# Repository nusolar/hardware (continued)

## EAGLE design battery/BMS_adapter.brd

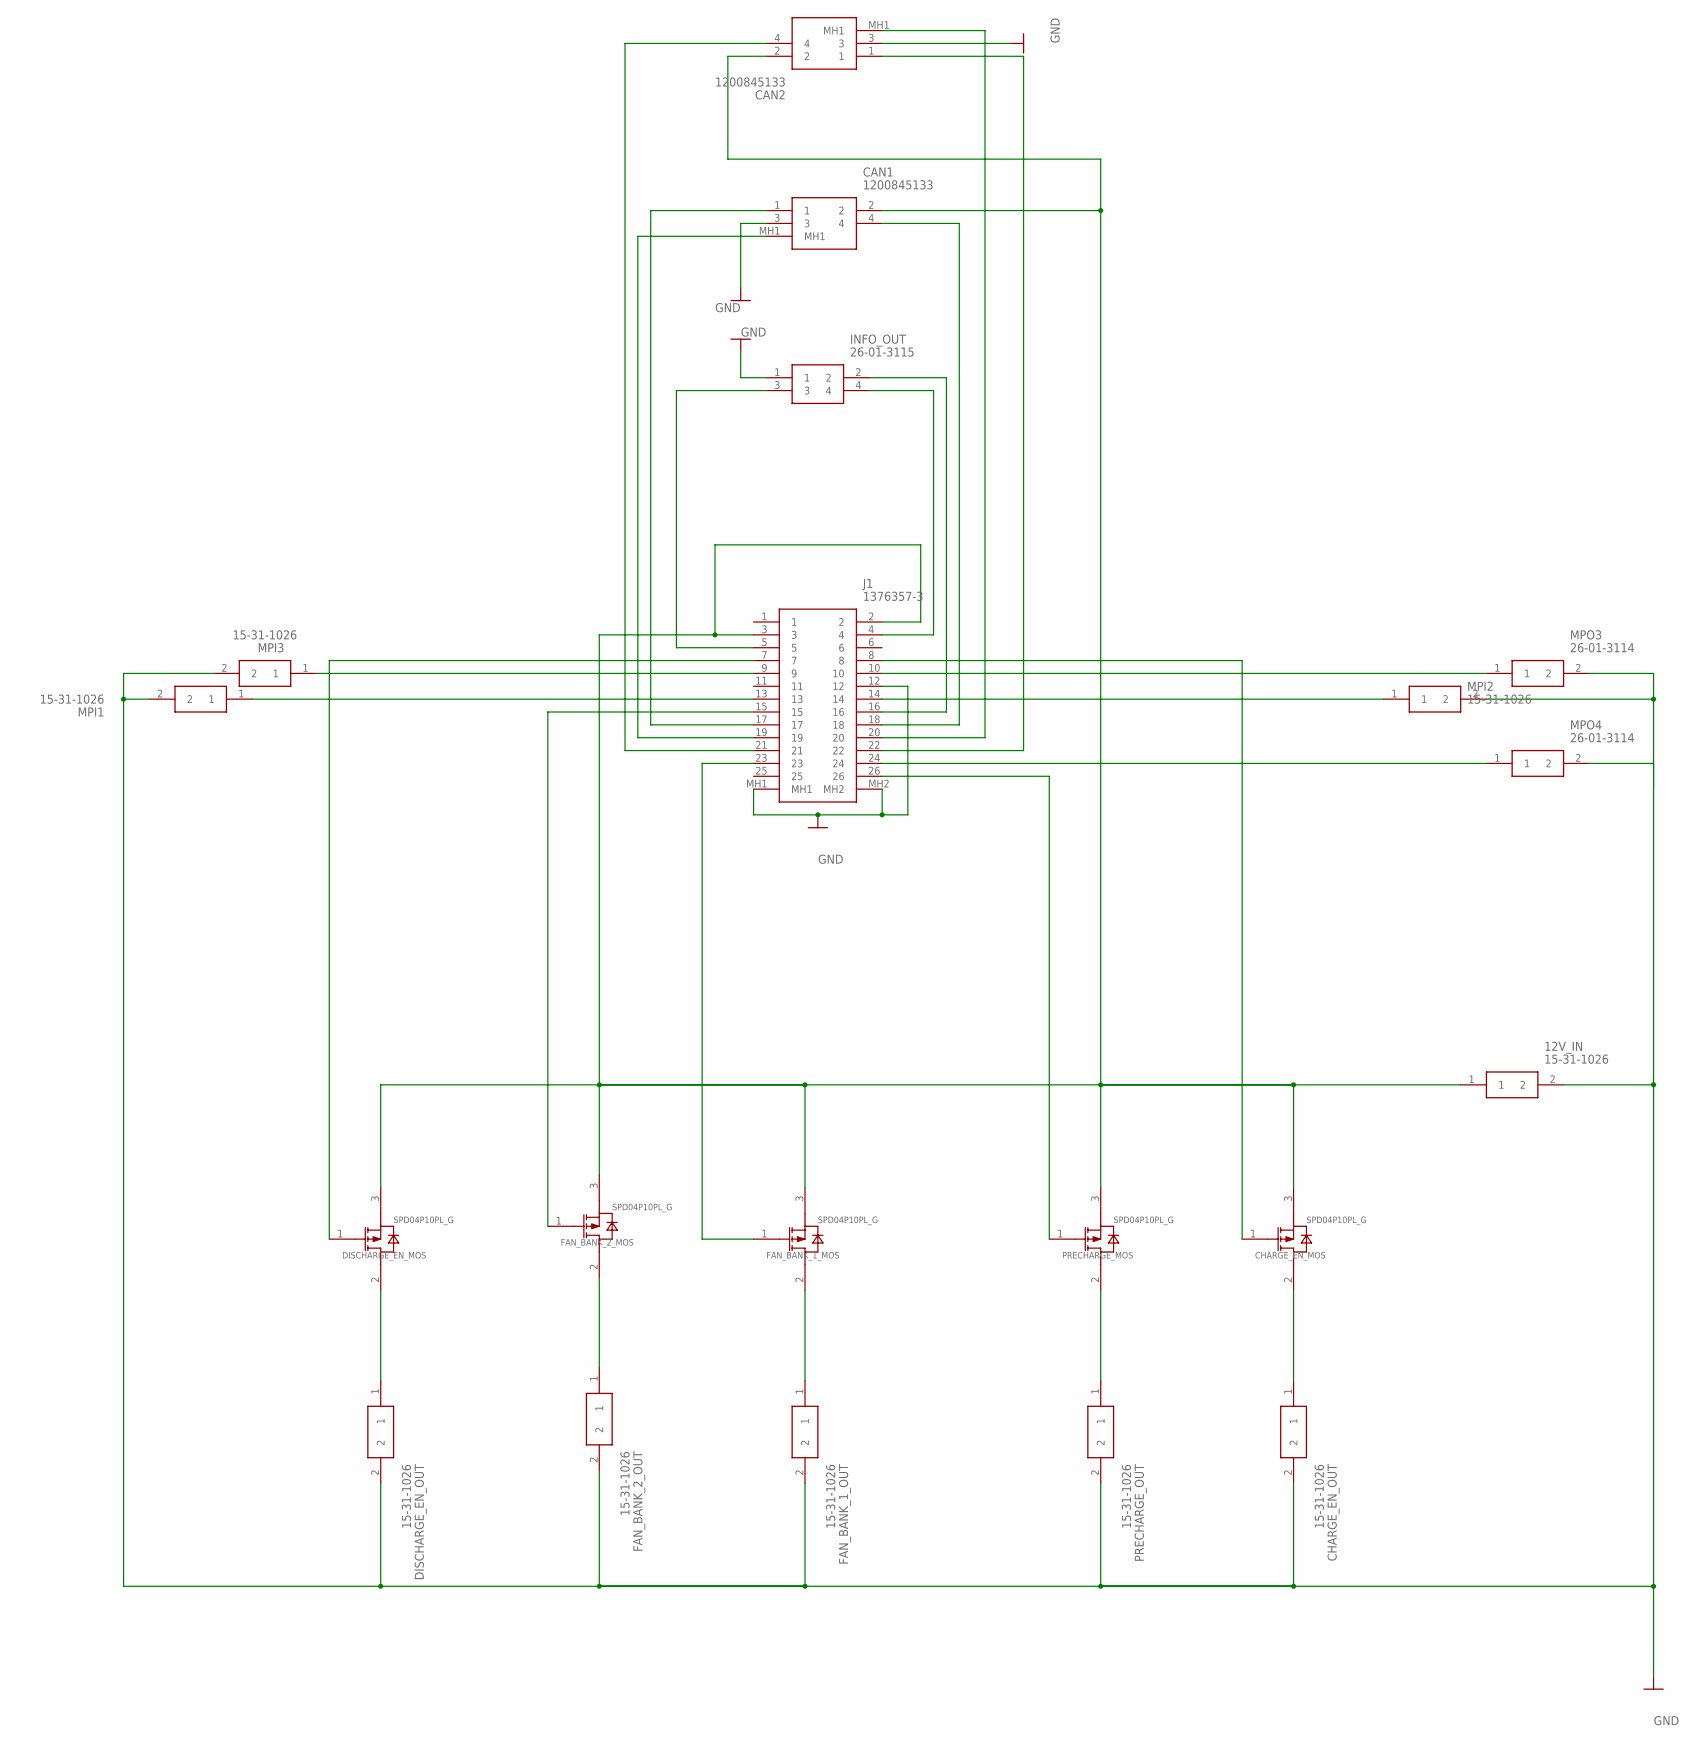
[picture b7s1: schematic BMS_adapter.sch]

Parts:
12V_IN: 15-31-1026; 15311026
CAN1, CAN2: 1200845133
CHARGE_EN_MOS: SPD04P10PL_G; TO229P994X241-3N
CHARGE_EN_OUT: 15-31-1026; 15311026
DISCHARGE_EN_MOS: SPD04P10PL_G; TO229P994X241-3N
DISCHARGE_EN_OUT: 15-31-1026; 15311026
FAN_BANK_1_MOS, FAN_BANK_2_MOS: SPD04P10PL_G; TO229P994X241-3N
FAN_BANK_1_OUT, FAN_BANK_2_OUT: 15-31-1026; 15311026
INFO_OUT: 26-01-3115; 39-30-1040
J1: 1376357-3; 13763573
MPI1, MPI2, MPI3: 15-31-1026; 15311026
MPO3, MPO4: 26-01-3114; 0026013114
PRECHARGE_MOS: SPD04P10PL_G; TO229P994X241-3N
PRECHARGE_OUT: 15-31-1026; 15311026

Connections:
GND: 12V_IN.2, CAN1.3, CAN2.3, CHARGE_EN_OUT.2, DISCHARGE_EN_OUT.2, FAN_BANK_1_OUT.2, FAN_BANK_2_OUT.2, INFO_OUT.1, J1.12, J1.MH1, J1.MH2, MPI1.2, MPI2.2, MPI3.2, MPO3.2, PRECHARGE_OUT.2
GND1: MPO4.2
unnamed: J1.26, PRECHARGE_MOS.1
unnamed: FAN_BANK_1_MOS.1, J1.23
unnamed: FAN_BANK_2_MOS.1, J1.15
unnamed: DISCHARGE_EN_MOS.1, J1.7
unnamed: 12V_IN.1, CAN1.2, CAN2.2, CHARGE_EN_MOS.3, DISCHARGE_EN_MOS.3, FAN_BANK_1_MOS.3, FAN_BANK_2_MOS.3, J1.2, J1.3, PRECHARGE_MOS.3
unnamed: J1.10, MPO3.1
unnamed: J1.9, MPI3.1
unnamed: J1.13, MPI1.1
unnamed: J1.14, MPI2.1
unnamed: J1.24, MPO4.1
unnamed: INFO_OUT.3, J1.5
unnamed: INFO_OUT.4, J1.4
unnamed: INFO_OUT.2, J1.16
unnamed: FAN_BANK_1_MOS.2, FAN_BANK_1_OUT.1
unnamed: CAN1.1, J1.17
unnamed: CAN1.4, J1.18
unnamed: CAN1.MH1, J1.19
unnamed: CAN2.1, J1.22
unnamed: CAN2.4, J1.21
unnamed: CAN2.MH1, J1.20
unnamed: DISCHARGE_EN_MOS.2, DISCHARGE_EN_OUT.1
unnamed: CHARGE_EN_MOS.1, J1.8
unnamed: FAN_BANK_2_MOS.2, FAN_BANK_2_OUT.1
unnamed: CHARGE_EN_MOS.2, CHARGE_EN_OUT.1
unnamed: PRECHARGE_MOS.2, PRECHARGE_OUT.1

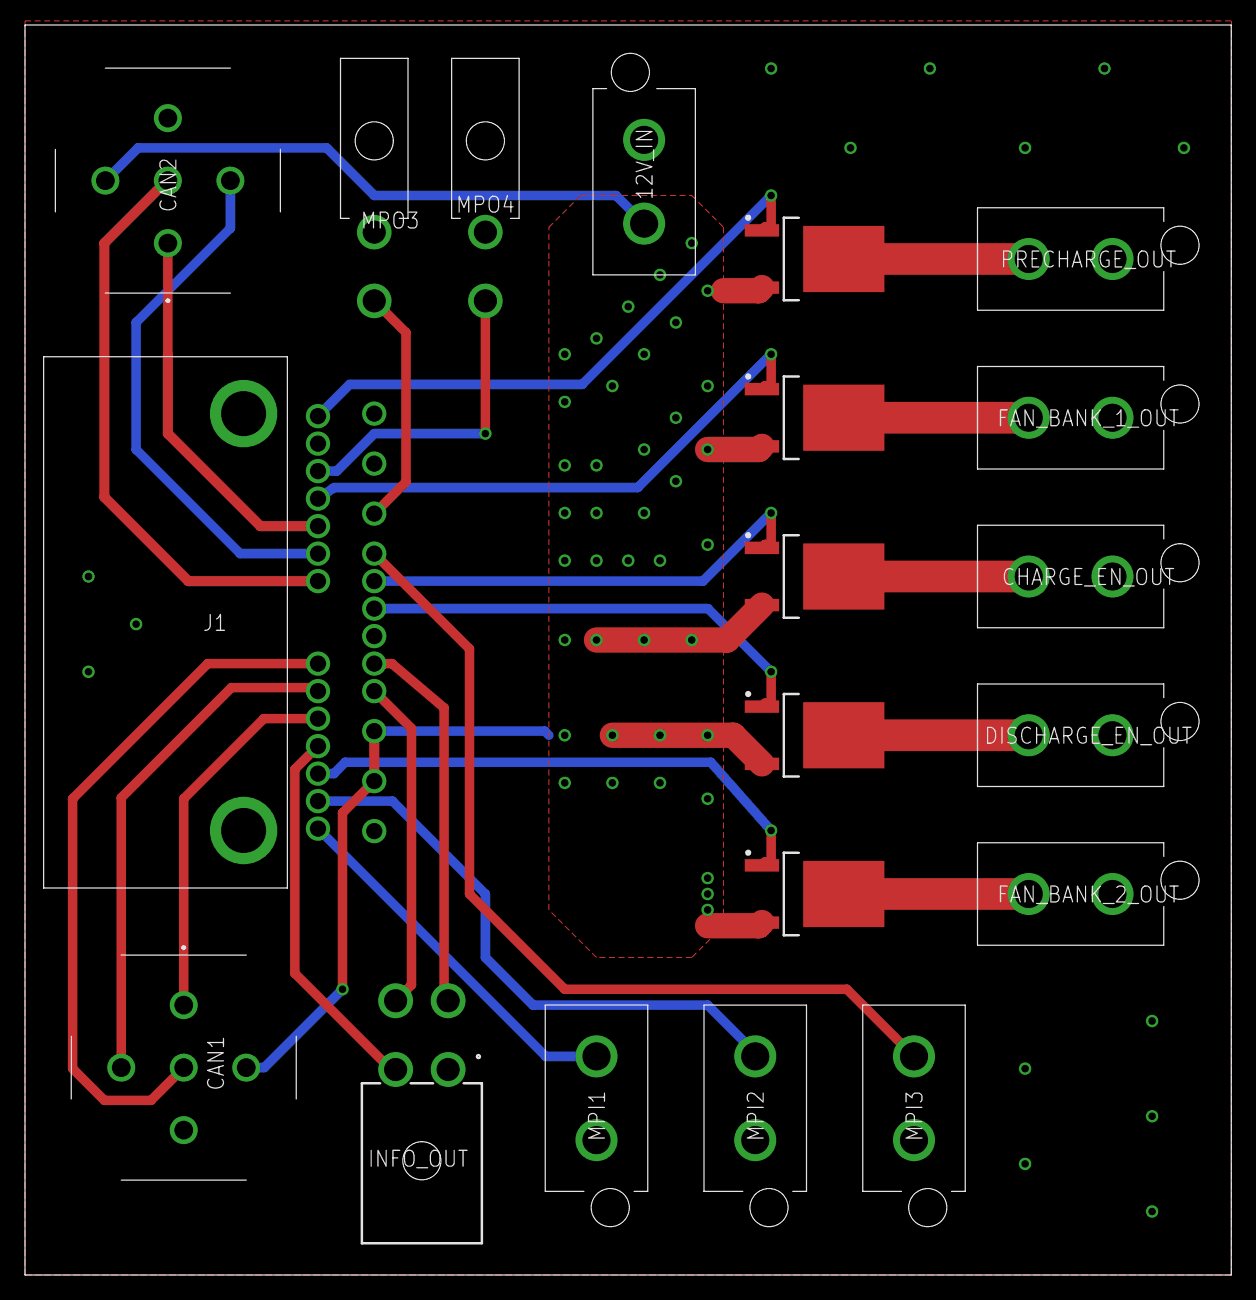
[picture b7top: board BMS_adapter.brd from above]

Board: 2 copper layers, 96.5 x 100.0 mm, 20 parts (0 on the bottom side), 26 nets.

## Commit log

2019-10-11 made a schematic. first commit. look at me.
2019-10-13 i did a thing it's cool
2019-10-13 correcrt lights
2019-10-25 Create DCDC_combined.sch
    Redesigned DCDC board. Spec'd for new Buck Converter. Its more fun now.
2019-10-27 Started modelling the cable-routing in the car.
2019-10-27 Test
2019-11-03 Power Supply Voltage Input
    Schematics, boards, and gerber file for power supply 1-10volt input.
2019-11-03 pulldown resistor
    added a pulldown resistor to analog pin
2019-11-03 Modified Arduino Uno
    Modified Arduino Uno; replaced USB and power jack with pin headers
2019-11-03 Modeled all low-power-connections in the car.
2019-11-03 driver control board w/ pulldown resistor
2019-11-03 updated_light_control
    light control
2019-11-08 New ARduino Board
2019-11-08 modified arduino
2019-11-10 schematic for dashboard and uno
    shows connectoin between dashboard and uno
2019-11-10 First version of BMS-contactor-contactor board.
2019-11-17 charlie done f***** up
2019-11-24 Designed PCB for BMS (unreviewed).
2019-11-25 Integrated DC Board with M0 Footprint
    This is one half of our integarted board plan. The other half includes the LCD board and the lightcontrol
2019-12-06 The real Final DCDC Board, pre trace laying
2019-12-06 Revert "Test"
    This reverts commit 3d1dbc2c878e3fb79790fd224c3c027493952d56.
2019-12-06 Revert "The real Final DCDC Board, pre trace laying"
    This reverts commit c670ee118606038cf509dcd0191e2f519553c8fe.
2019-12-06 DCDC FINAL PRE-TRACE LAYING
2019-12-06 DC-DC routing version 1
2019-12-29 added block diagram
2020-01-02 made DCDC traces thicc
    slid wires around to fix DRCs
    ready to fab
2020-01-03 DCDC - added top GND plane
2020-01-12 DCDC added CAN
    generated gerbers for a lot of stuff
2020-01-12 Create DCDCFinalBoardLayout_2020-01-12.zip
    Zip for PCBWay, to create the DCDC (direct current to direct current) printed circuit (a complete and closed path around which a circulating electric current can flow) board (for the solar car (SC7.5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
2020-01-12 DCDC Final Board Layout & Schematic
    The final iteration of a lengthy design process, involving input from a variety of parties, with specializations ranging from physics, to electrical engineering, to electrical engineering, to electri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
2020-01-12 left side of integrated board
    has the old driver control board with the m0 addalogger board
2020-01-16 final driver control side of integrated board
    final driver control (right side) of integrated board, should be ready for review
2020-01-16 updated dcdc 1/15
2020-01-16 u;date
2020-01-16 drver control side of board no DRC
    DRCs fixed, 12V power coming in from CAN connectors
2020-01-19 updated lightboard 2.1
    or gates' packages are different, going to have to add 3d packages and foot prints for or gates on PC at home cos mac kinda sucks
2020-01-20 Foot_print of LCD side integrated board
    Heres just the foot print for the Adalogger and the GPS model for the LCD side of the board
2020-01-20 updated gerber files with new diode
2020-01-21 changed linus' files to use the new BMS footprints.
2020-01-21 updated DCDC diode
    replaced insufficient SMD diode (in terms of current cap) with three TO220 diodes, with parallel dual configurations
2020-01-22 updated gerbers for DCDC and BMS adapter
    also added correct BOM for dc/dc
2020-01-26 fixed light board files
    ok ay do kay
2020-01-30 one more push
    Push
2020-02-02 pushed vdr reports
2020-02-02 final schematic, just routing now
2020-02-02 integrated board design review
    did gud stuff
    fixed logic power
    thigns were done
2020-02-09 NO DRC ERROR!
    YAY
2020-02-10 very minor tweak
2020-02-10 A few more minor (but very important) tweaks
2020-02-13 Handing off for charlie's review
2020-02-16 removed some dimensions that were on the copper layer, checked pinning. TODO: fix CAN pinout on the CAN interface connectors, follow linus' BMS issues
2020-02-16 ok i think its finally done
2020-02-17 ripped up hanging trace
2020-02-17 fixed airwire in fuse
2020-02-24 changed connectors to spare digital and analog to 90 degree 4 pin molex minifit
2020-02-24 BOM!
    for integrated
2020-09-12 organize
2020-09-12 remove race reports
    they should be in drive instead
2020-09-12 put datasheet in datasheet folder lmao
